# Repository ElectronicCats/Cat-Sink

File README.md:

# CatSink - USB power supply with PD

<p align="center">
    
</p>

<p align=center>

</p>

A USB-C PD Sink up to 20V 5A based on the Cypress CYPD3177 USB PD Controller

USB-C PD offers the option to negotiate power delivery from a compatible power supply. This board plays the role of a sink device, enabling any device to be powered by a USB power supply. Any type of power connector can be attached through a 2-pin screw terminal or directly soldered into the PCB for a lower profile. The voltage can be set to 5V, 9V, 12V, or 20V and the maximum negotiable current can be set to 1A, 2A, 3A, or 5A. Other voltage or current settings are possible by changing resistors. No programming is needed.

## How to contribute 
 Contributions are welcome! 

Please read the document  [**Contribution Manual**](https://github.com/ElectronicCats/electroniccats-cla/blob/main/electroniccats-contribution-manual.md)  which will show you how to contribute your changes to the project.

✨ Thanks to all our [contributors](https://github.com/ElectronicCats/Cat-Sink/graphs/contributors)! ✨

See [**_Electronic Cats CLA_**](https://github.com/ElectronicCats/electroniccats-cla/blob/main/electroniccats-cla.md) for more information.

See the  [**community code of conduct**](https://github.com/ElectronicCats/electroniccats-cla/blob/main/electroniccats-community-code-of-conduct.md) for a vision of the community we want to build and what we expect from it."						

## License

<br />This work is licensed under the <a rel="license" href="http://creativecommons.org/licenses/by-sa/4.0/">Creative Commons Attribution-ShareAlike 4.0 International License</a>.

Electronic Cats invests time and resources in providing this open-source design, please support Electronic Cats and open-source hardware by purchasing products from Electronic Cats!

Designed by Electronic Cats.

Firmware released under an GNU AGPL v3.0 license. See the LICENSE file for more information.

Hardware released under an CERN Open Hardware Licence v1.2. See the LICENSE_HARDWARE file for more information.

Electronic Cats is a registered trademark, please do not use it if you sell these PCBs.

Octuber 2020

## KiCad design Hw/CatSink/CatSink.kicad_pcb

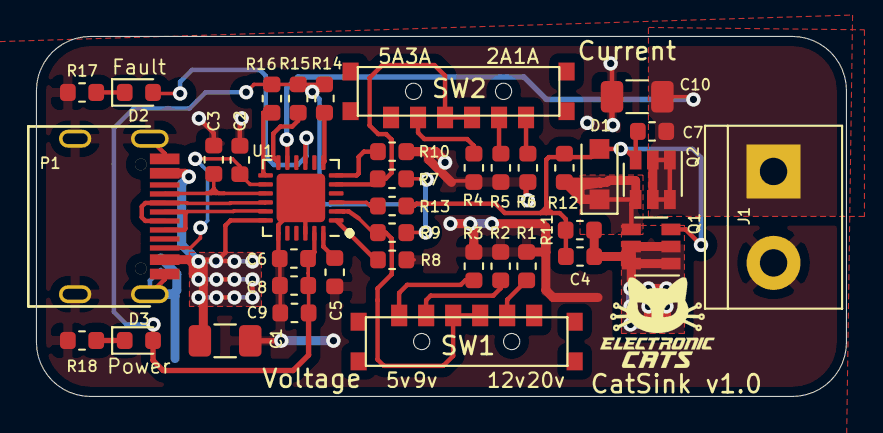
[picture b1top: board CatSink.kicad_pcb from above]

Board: 2 copper layers, 45.0 x 20.0 mm, 38 parts (0 on the bottom side), 28 nets.

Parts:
C1, C10: 3.3uF; C_1206_3216Metric
C2, C3: 390pF; C_0603_1608Metric
C4, C5, C6, C7: 1uF; C_0603_1608Metric
C8, C9: 0.1uF; C_0603_1608Metric
D1: NZH10C; D_SOD-123F
D2: Fault; LED_0603_1608Metric
D3: Power; LED_0603_1608Metric
J1: Vout; TerminalBlock_bornier-2_P5.08mm
P1: USB_C_Plug_USB2.0; C393939
Q1, Q2: SI3421DV; SOT-23-6
R1, R5: 2.4K; R_0603_1608Metric
R2, R6, R13, R18: 1K; R_0603_1608Metric
R3: 0R; R_0603_1608Metric
R4, R7, R8, R9, R10: 5.1K; R_0603_1608Metric
R11, R14, R15, R16, R17: 10K; R_0603_1608Metric
R12: 50K; R_0603_1608Metric
SW1: Voltage; K3-1410S-E1
SW2: Current; K3-1410S-E1
U1: CYPD3177-24LQXI; QFN-24-1EP_4x4mm_P0.5mm_EP2.7x2.7mm

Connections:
+3V3: C6.1, C8.1, C9.1, D3.2, R7.1, R9.1, R14.1, R15.1, R16.1, U1.23
+VSW: C7.1, C10.1, J1.1, Q2.1, Q2.2, Q2.5, Q2.6, U1.11
/1A: R6.1, SW2.1
/2A: R5.1, SW2.2
/3A: R4.1, SW2.5
/5v: R3.1, SW1.1
/9v: R2.1, SW1.2
/12v: R1.1, SW1.5
/CC1: C3.1, P1.A5, U1.15
/CC2: C2.1, P1.B5, U1.14
/D+: P1.A6, U1.17
/D-: P1.A7, U1.16
/Fault: D2.2, U1.9
/Icoarse: R7.2, SW2.3, SW2.4, U1.5
/Vmax: R9.2, SW1.3, SW1.4, U1.2
GND: C1.2, C2.2, C3.2, C5.2, C6.2, C8.2, C9.2, C10.2, J1.2, P1.A1, P1.S1, R1.2, R2.2, R3.2, R4.2, R5.2, R6.2, R8.2, R10.2, R17.2, R18.2, U1.19, U1.22, U1.25
unnamed: C4.2, C7.2, D1.2, Q1.3, Q2.3, R11.2, R12.2, R13.1
unnamed: C5.1, U1.24
unnamed: D1.1, Q1.4, Q2.4, R12.1
unnamed: D2.1, R17.1
unnamed: D3.1, R18.1
unnamed: R8.1, U1.1
unnamed: R10.1, U1.6
unnamed: R13.2, U1.3
unnamed: R14.2, U1.7
unnamed: R15.2, U1.12
unnamed: R16.2, U1.13
VBUS: C1.1, C4.1, P1.A4, Q1.1, Q1.2, Q1.5, Q1.6, R11.1, U1.18

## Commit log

2020-10-24 add project v1.0
2020-10-24 fix traces add gitignore
2020-10-25 fix pcb
2020-10-26 added logos
2020-10-26 Create LICENSE
2020-10-27 Added Led and 3D switch
2020-10-27 fix traces
2020-11-27 update BOM
2021-01-20 update kicad project
2023-10-24 Updated Missing translations
2023-12-26 Format updated
    The readme format has been updated.
2024-04-11 feat(docs):Update README.md
    Add how to contribute
2024-04-29 fix (hw): change notations from margin to user drawings
